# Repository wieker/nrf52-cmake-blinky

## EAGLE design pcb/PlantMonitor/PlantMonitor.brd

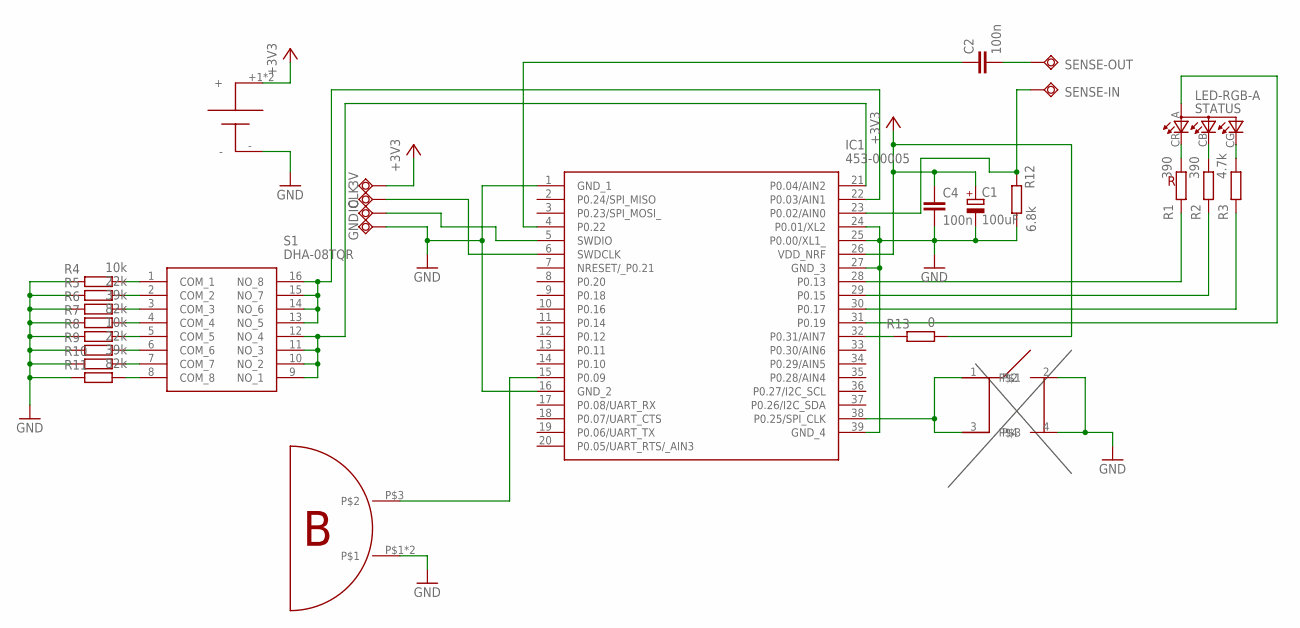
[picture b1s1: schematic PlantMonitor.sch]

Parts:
3V: TPSQB1,27; B1,27
C1: 100uF; A/3216-18W
C2, C4: 100n; C0603K
CLK: TPSQB1,27; B1,27
GND: TPSQB1,27; B1,27
IC1: 453-00005; 45300005
IO: TPSQB1,27; B1,27
R1, R2: 390; R0603
R3: 4.7k; R0603
R4, R8: 10k; R0603
R5, R9: 22k; R0603
R6, R10: 39k; R0603
R7, R11: 82k; R0603
R12: 6.8k; R0603
R13: 0; R0603
S1: DHA-08TQR; SOIC127P810X230-16N
SENSE-IN: TPSQB1,27; B1,27
SENSE-OUT: TPSQB1,27; B1,27
STATUS: LED-RGB-A
U$1: PTS525SK08SMTR2LFS
U$2: COIN-CELL-HOLDER
U$3: MICRO-BUZZER

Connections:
+3V3: 3V.TP, C1.+, C4.1, IC1.26 (VDD_NRF), R13.2, U$2.+1 (+), U$2.+2 (+)
GND: C1.-, C4.2, GND.TP, IC1.1 (GND_1), IC1.16 (GND_2), IC1.24 (P0.01/XL2), IC1.25 (P0.00/XL1_), IC1.27 (GND_3), IC1.39 (GND_4), R4.1, R5.1, R6.1, R7.1, R8.1, R9.1, R10.1, R11.1, R12.2, U$1.2, U$1.4, U$2.-, U$3.P$1, U$3.P$2
LED-VCC: IC1.31 (P0.19), STATUS.A
unnamed: IC1.15 (P0.09), U$3.P$3
unnamed: IC1.5 (SWDIO), IO.TP
unnamed: CLK.TP, IC1.6 (SWDCLK)
unnamed: IC1.22 (P0.03/AIN1), S1.13 (NO_5), S1.14 (NO_6), S1.15 (NO_7), S1.16 (NO_8)
unnamed: IC1.21 (P0.04/AIN2), S1.9 (NO_1), S1.10 (NO_2), S1.11 (NO_3), S1.12 (NO_4)
unnamed: R4.2, S1.1 (COM_1)
unnamed: R5.2, S1.2 (COM_2)
unnamed: R6.2, S1.3 (COM_3)
unnamed: R7.2, S1.4 (COM_4)
unnamed: R8.2, S1.5 (COM_5)
unnamed: R9.2, S1.6 (COM_6)
unnamed: IC1.38 (P0.25/SPI_CLK), U$1.1, U$1.3
unnamed: R10.2, S1.7 (COM_7)
unnamed: R3.2, STATUS.CG (CGREEN)
unnamed: R1.2, STATUS.CR (CRED)
unnamed: C2.1, IC1.4 (P0.22)
unnamed: R11.2, S1.8 (COM_8)
unnamed: IC1.32 (P0.31/AIN7), R13.1
unnamed: R2.2, STATUS.CB (CBLUE)
unnamed: IC1.29 (P0.15), R2.1
unnamed: IC1.28 (P0.13), R1.1
unnamed: IC1.30 (P0.17), R3.1
SENSE-IN: IC1.23 (P0.02/AIN0), R12.1, SENSE-IN.TP
SENSE-OUT: C2.2, SENSE-OUT.TP

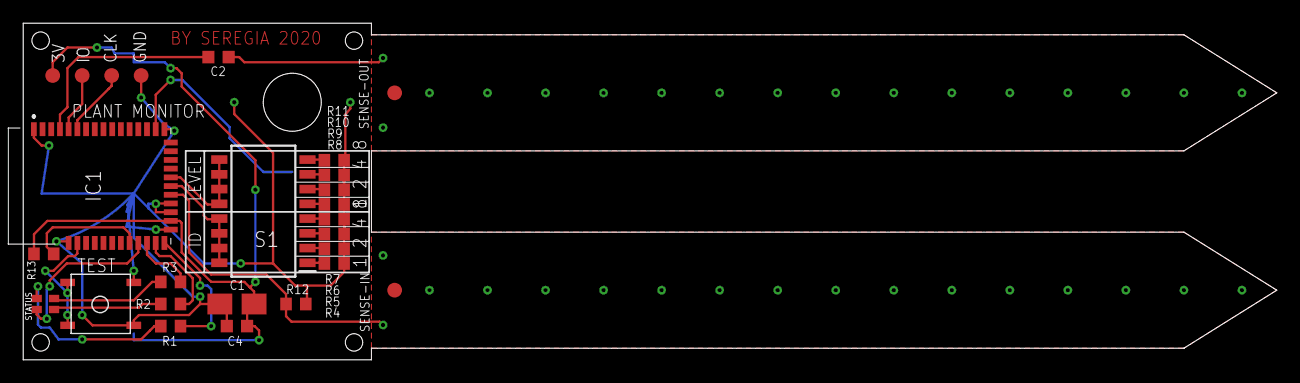
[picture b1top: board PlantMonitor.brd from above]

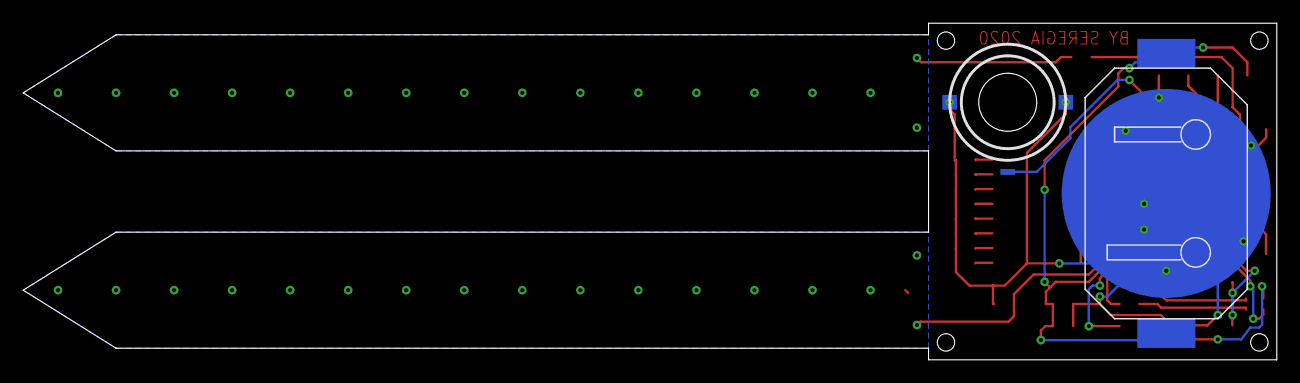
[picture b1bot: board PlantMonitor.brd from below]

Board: 2 copper layers, 108.0 x 29.0 mm, 28 parts (2 on the bottom side), 27 nets.

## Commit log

2020-01-09 Build for nRF52832
2020-01-09 Build for nRF52810
2020-01-09 Build for nRF52832: BLE #1
2020-01-09 Build for nRF52832: BLE #2
2020-01-11 BLE example beacon for nRF52-DK
2020-01-12 nRF52810 BLE#1: just blink
2020-01-12 nRF52810 BLE#1: just blink #2
2020-01-12 nRF52810 BLE#1: just blink #3
2020-01-12 nRF52810 BLE#1: just blink #4 with BSP API
2020-01-12 nRF52810 BLE#1: just blink #4 with s132 softdevice
2020-01-12 nRF52810 BLE#1: started with RC LF ans s132 on custom board
2020-01-12 nRF52832: proprietary test
2020-01-17 nRF52832: UART
2020-01-17 nRF52832: I2C scan
2020-01-18 nRF52832: got the response according to the HTS221 datasheet
2020-01-23 nRF52832: interface with the HTS221
2020-01-28 Started flash script
2020-01-29 OpenOCD scripts for two boards
2020-01-29 UART on nRF52-DK
2020-01-29 nRF52-DK direct RX
2020-01-29 nRF52-DK UART RF
2020-01-29 txver
2020-01-29 rxver
2020-02-13 blink1
2020-02-13 blink2
2020-02-13 two-way comm
2020-02-16 simple alg
2020-02-19 improved makefile
2020-03-11 experiments with nRF52 UART => cp2102 on custom board (see other project for KiCAD sources)
2020-03-11 changed CMake to support OpenOCD flash target
2020-03-11 trying to debug UART
2020-03-15 trying to debug blink on the new board
2020-03-15 trying to debug UART on the new board
2020-03-15 nRF52 module => OM13088 Board UART works
2020-03-15 nRF52 module UART on the custom board works
2020-03-21 Environment adoptation
2020-03-25 Working example of ble_app_blinky ported to custom board with NRF52810
2020-03-25 Clean up
2020-04-01 Compiling zigbee test project
2020-04-01 tests
2020-04-25 ESB + safe mode about 100uA
2020-04-25 Added soilMoistureSensor_setup
2020-05-26 Project restructure and PCB creation
2020-06-04 Adopted to the new board
2020-06-08 nRf52 => Atmel SAMD11 uart tx work
2020-06-08 nRf52 => Atmel SAMD11 uart tx changed speed to 9600
2020-06-13 Code adoptation for new board - low battery detection - reading ID and sensitivity keys using 2 analogue inputs - improved status indication
